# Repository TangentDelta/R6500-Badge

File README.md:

# R6500 Badge

## A simple wearable namebadge based on the Rockwell R6500 microcontroller

`6500badge-KiCAD` contains the CAD files for this project.
`Sample Program` contains some test code for the badge

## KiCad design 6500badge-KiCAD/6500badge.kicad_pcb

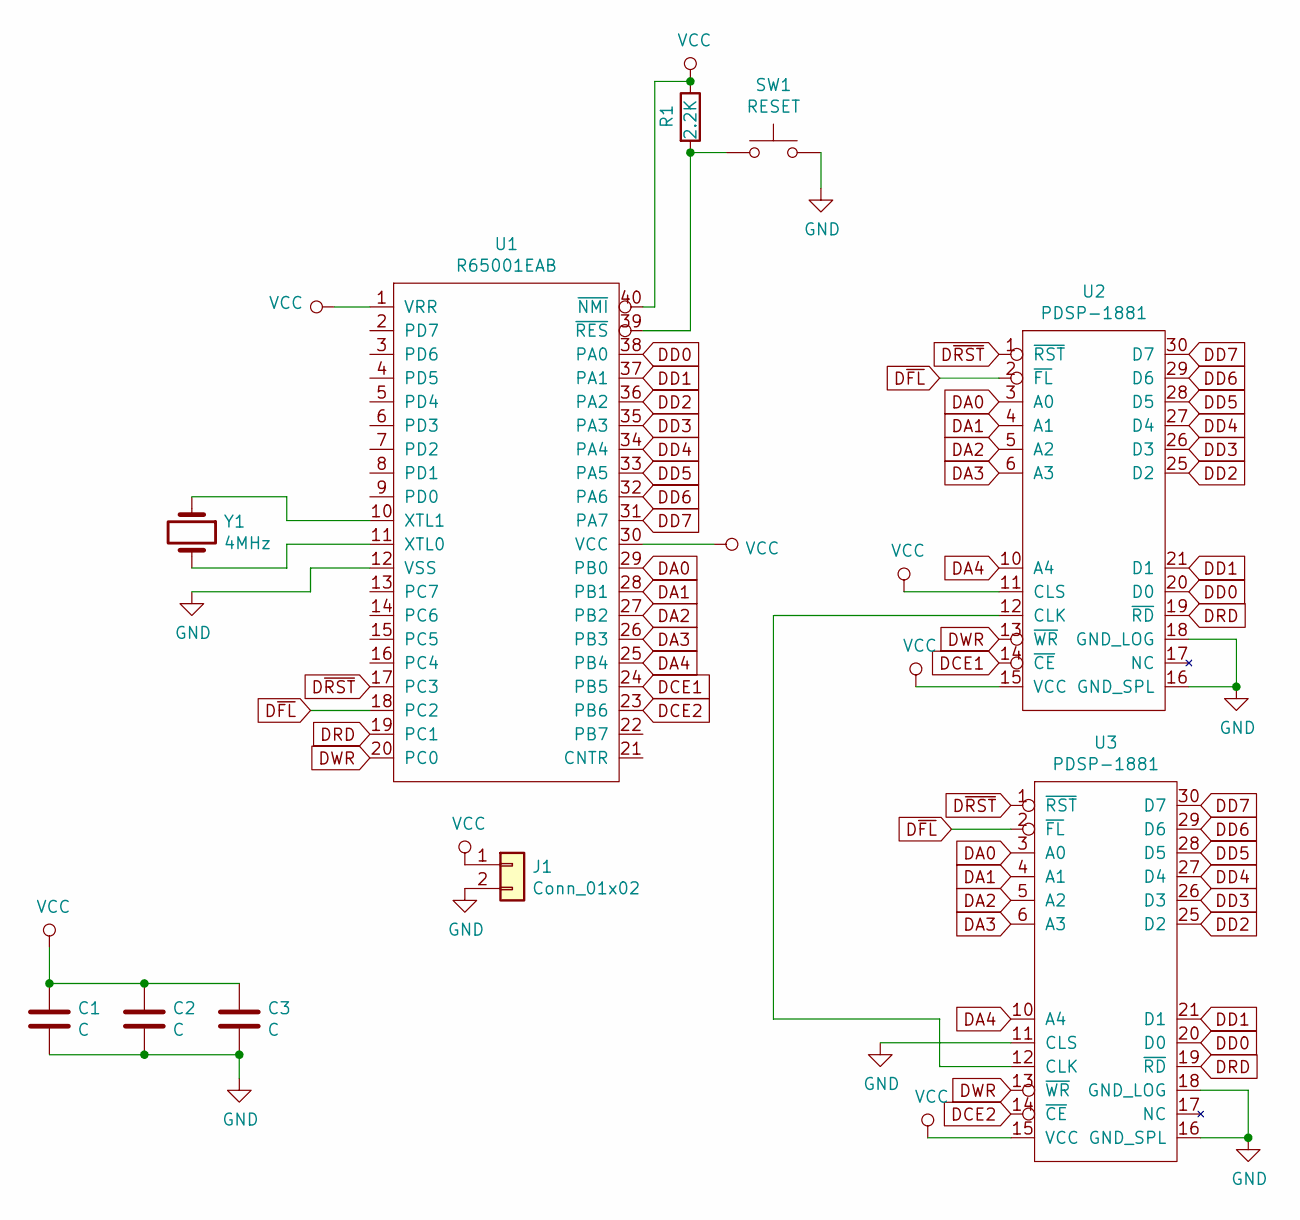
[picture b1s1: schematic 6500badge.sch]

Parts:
C1, C2, C3: C; C_Disc_D7.5mm_W2.5mm_P5.00mm
J1: Conn_01x02; PinHeader_1x02_P2.54mm_Vertical
R1: 2.2K; R_Axial_DIN0207_L6.3mm_D2.5mm_P10.16mm_Horizontal
SW1: RESET; SW_PUSH_6mm
U1: R65001EAB; DIP-40_W15.24mm_LongPads
U2, U3: PDSP-1881; DIP-30_W7.62mm
Y1: 4MHz; Crystal_HC18-U_Horizontal

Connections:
DA0: U1.29 (PB0), U2.3 (A0), U3.3 (A0)
DA1: U1.28 (PB1), U2.4 (A1), U3.4 (A1)
DA2: U1.27 (PB2), U2.5 (A2), U3.5 (A2)
DA3: U1.26 (PB3), U2.6 (A3), U3.6 (A3)
DA4: U1.25 (PB4), U2.10 (A4), U3.10 (A4)
DCE1: U1.24 (PB5), U2.14 (~CE)
DCE2: U1.23 (PB6), U3.14 (~CE)
DD0: U1.38 (PA0), U2.20 (D0), U3.20 (D0)
DD1: U1.37 (PA1), U2.21 (D1), U3.21 (D1)
DD2: U1.36 (PA2), U2.25 (D2), U3.25 (D2)
DD3: U1.35 (PA3), U2.26 (D3), U3.26 (D3)
DD4: U1.34 (PA4), U2.27 (D4), U3.27 (D4)
DD5: U1.33 (PA5), U2.28 (D5), U3.28 (D5)
DD6: U1.32 (PA6), U2.29 (D6), U3.29 (D6)
DD7: U1.31 (PA7), U2.30 (D7), U3.30 (D7)
DRD: U1.19 (PC1), U2.19 (~RD), U3.19 (~RD)
DWR: U1.20 (PC0), U2.13 (~WR), U3.13 (~WR)
D~FL: U1.18 (PC2), U2.2 (~FL), U3.2 (~FL)
D~RST: U1.17 (PC3), U2.1 (~RST), U3.1 (~RST)
GND: C1.2, C2.2, C3.2, J1.2, SW1.2, U1.12 (VSS), U2.16 (GND_SPL), U2.18 (GND_LOG), U3.11 (CLS), U3.16 (GND_SPL), U3.18 (GND_LOG)
unnamed: R1.2, SW1.1, U1.39 (~RES)
unnamed: U1.10 (XTL1), Y1.1
unnamed: U1.11 (XTL0), Y1.2
unnamed: U2.12 (CLK), U3.12 (CLK)
VCC: C1.1, C2.1, C3.1, J1.1, R1.1, U1.1 (VRR), U1.30 (VCC), U1.40 (~NMI), U2.11 (CLS), U2.15 (VCC), U3.15 (VCC)

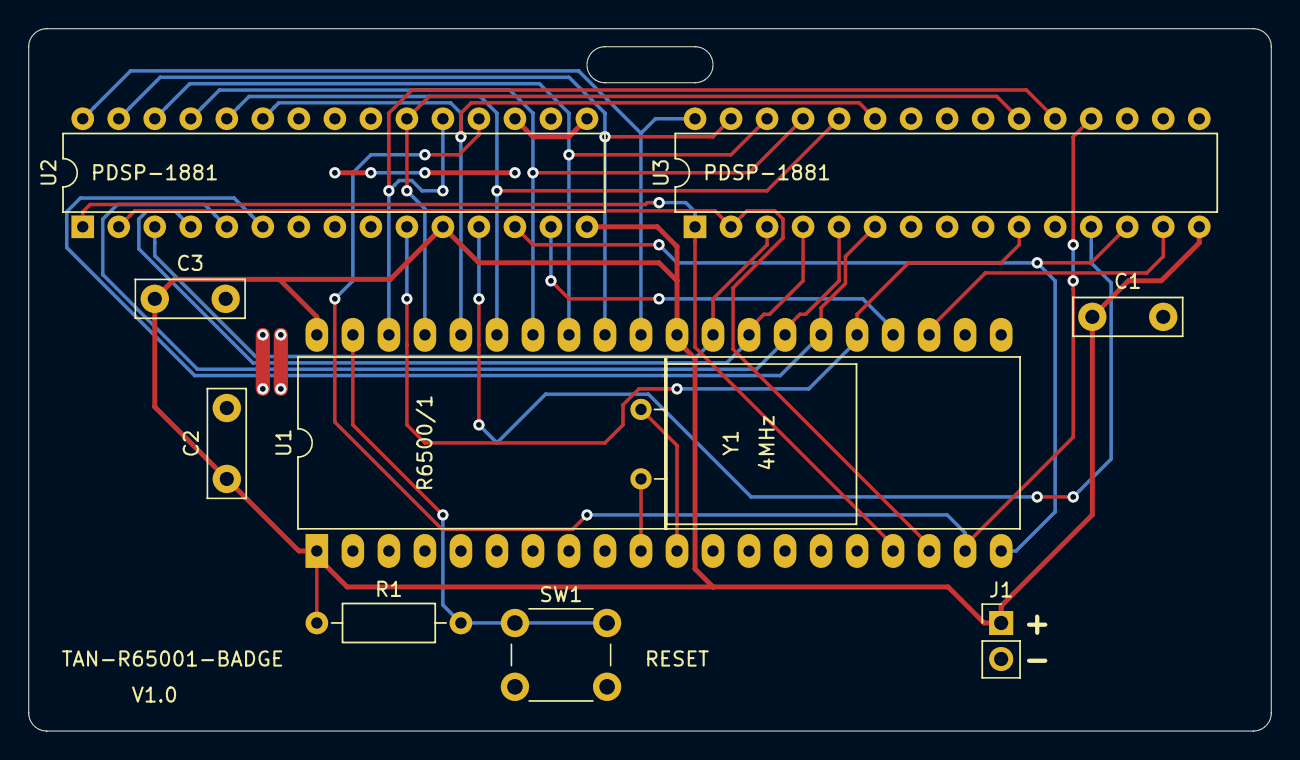
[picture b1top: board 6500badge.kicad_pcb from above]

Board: 2 copper layers, 87.6 x 49.5 mm, 10 parts (0 on the bottom side), 25 nets.

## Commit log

2021-10-06 Moved README.md
2021-10-06 Starting work on new program
